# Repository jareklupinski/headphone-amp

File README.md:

# headphone-amp
A simple headphone amp / signal buffer for balanced audio sources.

This design uses a TPS65131 to generate +-15V from a USB-C 5V input.

Originally, I wanted to use the INA1620, as its datasheet basically spells out that its intended use is as a headphone driver.

The opamp OPA1612 was chosen instead, as it seems to be basically the same chip, but without the integrated resistors, and was available from my assembly house at the time of production.

The PCB and face/backplates are sized for https://www.digikey.com/en/products/detail/bud-industries/EXN-23350-RDP/5886285, but any color should work ;)

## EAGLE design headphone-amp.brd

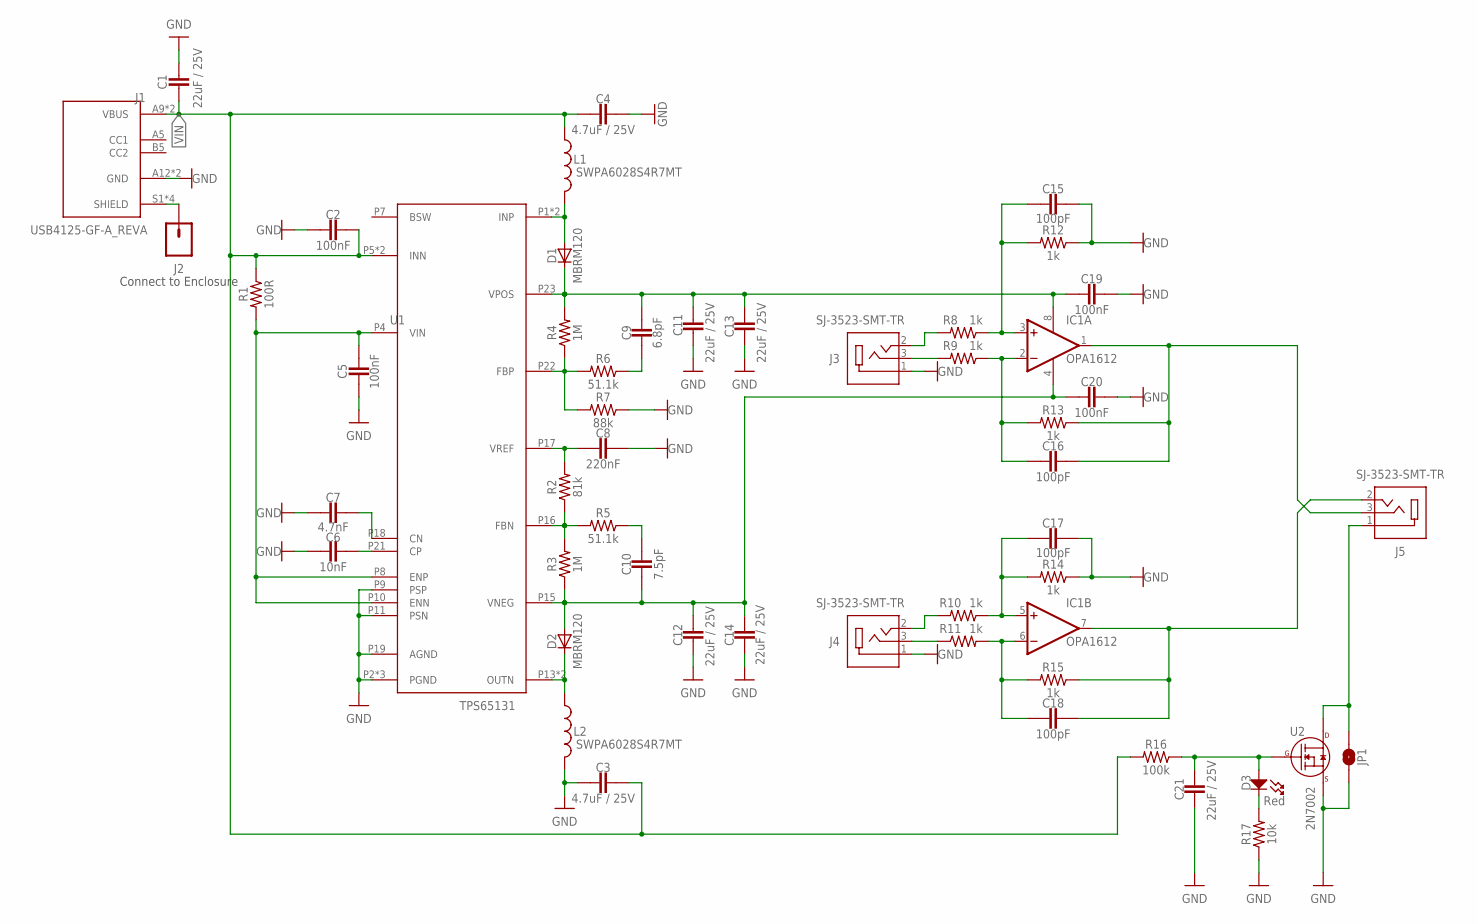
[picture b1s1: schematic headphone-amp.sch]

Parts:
C1, C11, C12, C13, C14, C21: 22uF / 25V; C0805
C2, C5, C19, C20: 100nF; C0402
C3, C4: 4.7uF / 25V; C0402
C6: 10nF; C0402
C7: 4.7nF; C0402
C8: 220nF; C0402
C9: 6.8pF; C0402
C10: 7.5pF; C0402
C15, C16, C17, C18: 100pF; C0402
D1, D2: MBRM120; POWERMITE
D3: Red; LED0603
IC1: OPA1612; SO08
J1: USB4125-GF-A_REVA; GCT_USB4125-GF-A_REVA
J2: CONN_01; 1X01
J3, J4, J5: SJ-3523-SMT-TR; CUI_SJ-3523-SMT-TR
JP1: JUMPER-SMT_2_NO_SILK; SMT-JUMPER_2_NO_SILK
L1, L2: SWPA6028S4R7MT; POWER-CHOKE_WE-TPC
R1: 100R; R0402
R2: 81k; R0402
R3, R4: 1M; R0402
R5, R6: 51.1k; R0402
R7: 88k; R0402
R8, R9, R10, R11, R12, R13, R14, R15: 1k; R0402
R16: 100k; R0402
R17: 10k; R0402
U1: TPS65131; QFN24-4X4-2
U2: 2N7002; SOT-23-3

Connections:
GND: C1.1, C2.1, C3.2, C4.1, C5.2, C6.2, C7.2, C8.1, C11.2, C12.2, C13.2, C14.2, C15.1, C17.1, C19.2, C20.2, C21.2, J1.A12 (GND), J1.B12 (GND), J3.1, J4.1, JP1.1, L2.2, R7.1, R12.1, R14.1, R17.1, U1.P2 (PGND), U1.P3 (PGND), U1.P9 (PSP), U1.P11 (PSN), U1.P19 (AGND), U1.PAD (PGND), U2.P$2 (SOURCE)
unnamed: C18.1, IC1.7 (OUT), J5.2, R15.1
unnamed: D1.P$2 (A), L1.2, U1.P1 (INP), U1.P24 (INP)
unnamed: C16.1, IC1.1 (OUT), J5.3, R13.1
unnamed: J1.S1 (SHIELD), J1.S2 (SHIELD), J1.S3 (SHIELD), J1.S4 (SHIELD), J2.1
unnamed: J3.3, R9.2
unnamed: R4.1, R6.2, R7.2, U1.P22 (FBP)
unnamed: C9.2, R6.1
unnamed: C8.2, R2.2, U1.P17 (VREF)
unnamed: R2.1, R3.2, R5.2, U1.P16 (FBN)
unnamed: C10.2, R5.1
unnamed: J3.2, R8.2
unnamed: D2.P$1 (C), L2.1, U1.P13 (OUTN), U1.P14 (OUTN)
unnamed: C6.1, U1.P21 (CP)
unnamed: C7.1, U1.P18 (CN)
unnamed: C18.2, IC1.6 (-IN), R11.2, R15.2
unnamed: C17.2, IC1.5 (+IN), R10.1, R14.2
unnamed: J4.2, R10.2
unnamed: J4.3, R11.1
unnamed: D3.CATHODE, R17.2
unnamed: C16.2, IC1.2 (-IN), R9.1, R13.2
unnamed: C15.2, IC1.3 (+IN), R8.1, R12.2
unnamed: C5.1, R1.2, U1.P4 (VIN), U1.P8 (ENP), U1.P10 (ENN)
unnamed: J5.1, JP1.2, U2.P$3 (DRAIN)
unnamed: C21.1, D3.ANODE, R16.1, U2.P$1 (GATE)
VDD: C9.1, C11.1, C13.1, C19.1, D1.P$1 (C), IC1.8 (V+), R4.2, U1.P23 (VPOS)
VEE: C10.1, C12.1, C14.1, C20.1, D2.P$2 (A), IC1.4 (V-), R3.1, U1.P15 (VNEG)
VIN: C1.2, C2.2, C3.1, C4.2, J1.A9 (VBUS), J1.B9 (VBUS), L1.1, R1.1, R16.2, U1.P5 (INN), U1.P6 (INN)

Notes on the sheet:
Connect to Enclosure

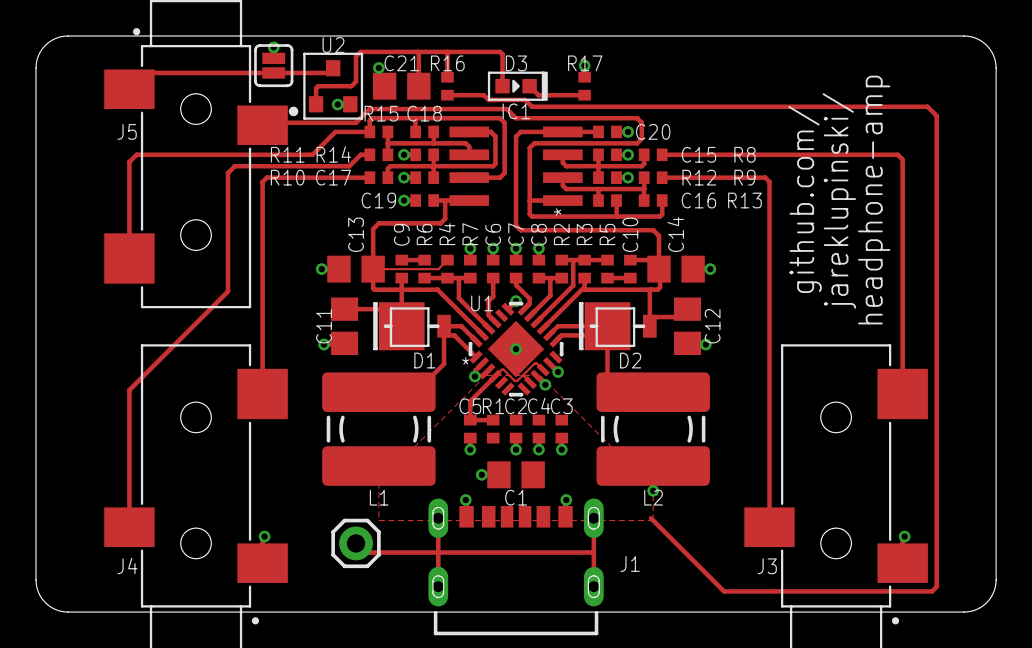
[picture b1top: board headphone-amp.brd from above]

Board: 2 copper layers, 53.3 x 32.0 mm, 52 parts (0 on the bottom side), 28 nets.

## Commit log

2021-12-05 add power led, add soft start, fix op amp polarity
2021-12-05 little routing change

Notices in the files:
parts and their libraries:
SparkFun-Connectors: Licensing: Creative Commons ShareAlike 4.0 International - https://creativecommons.org/licenses/by-sa/4.0
